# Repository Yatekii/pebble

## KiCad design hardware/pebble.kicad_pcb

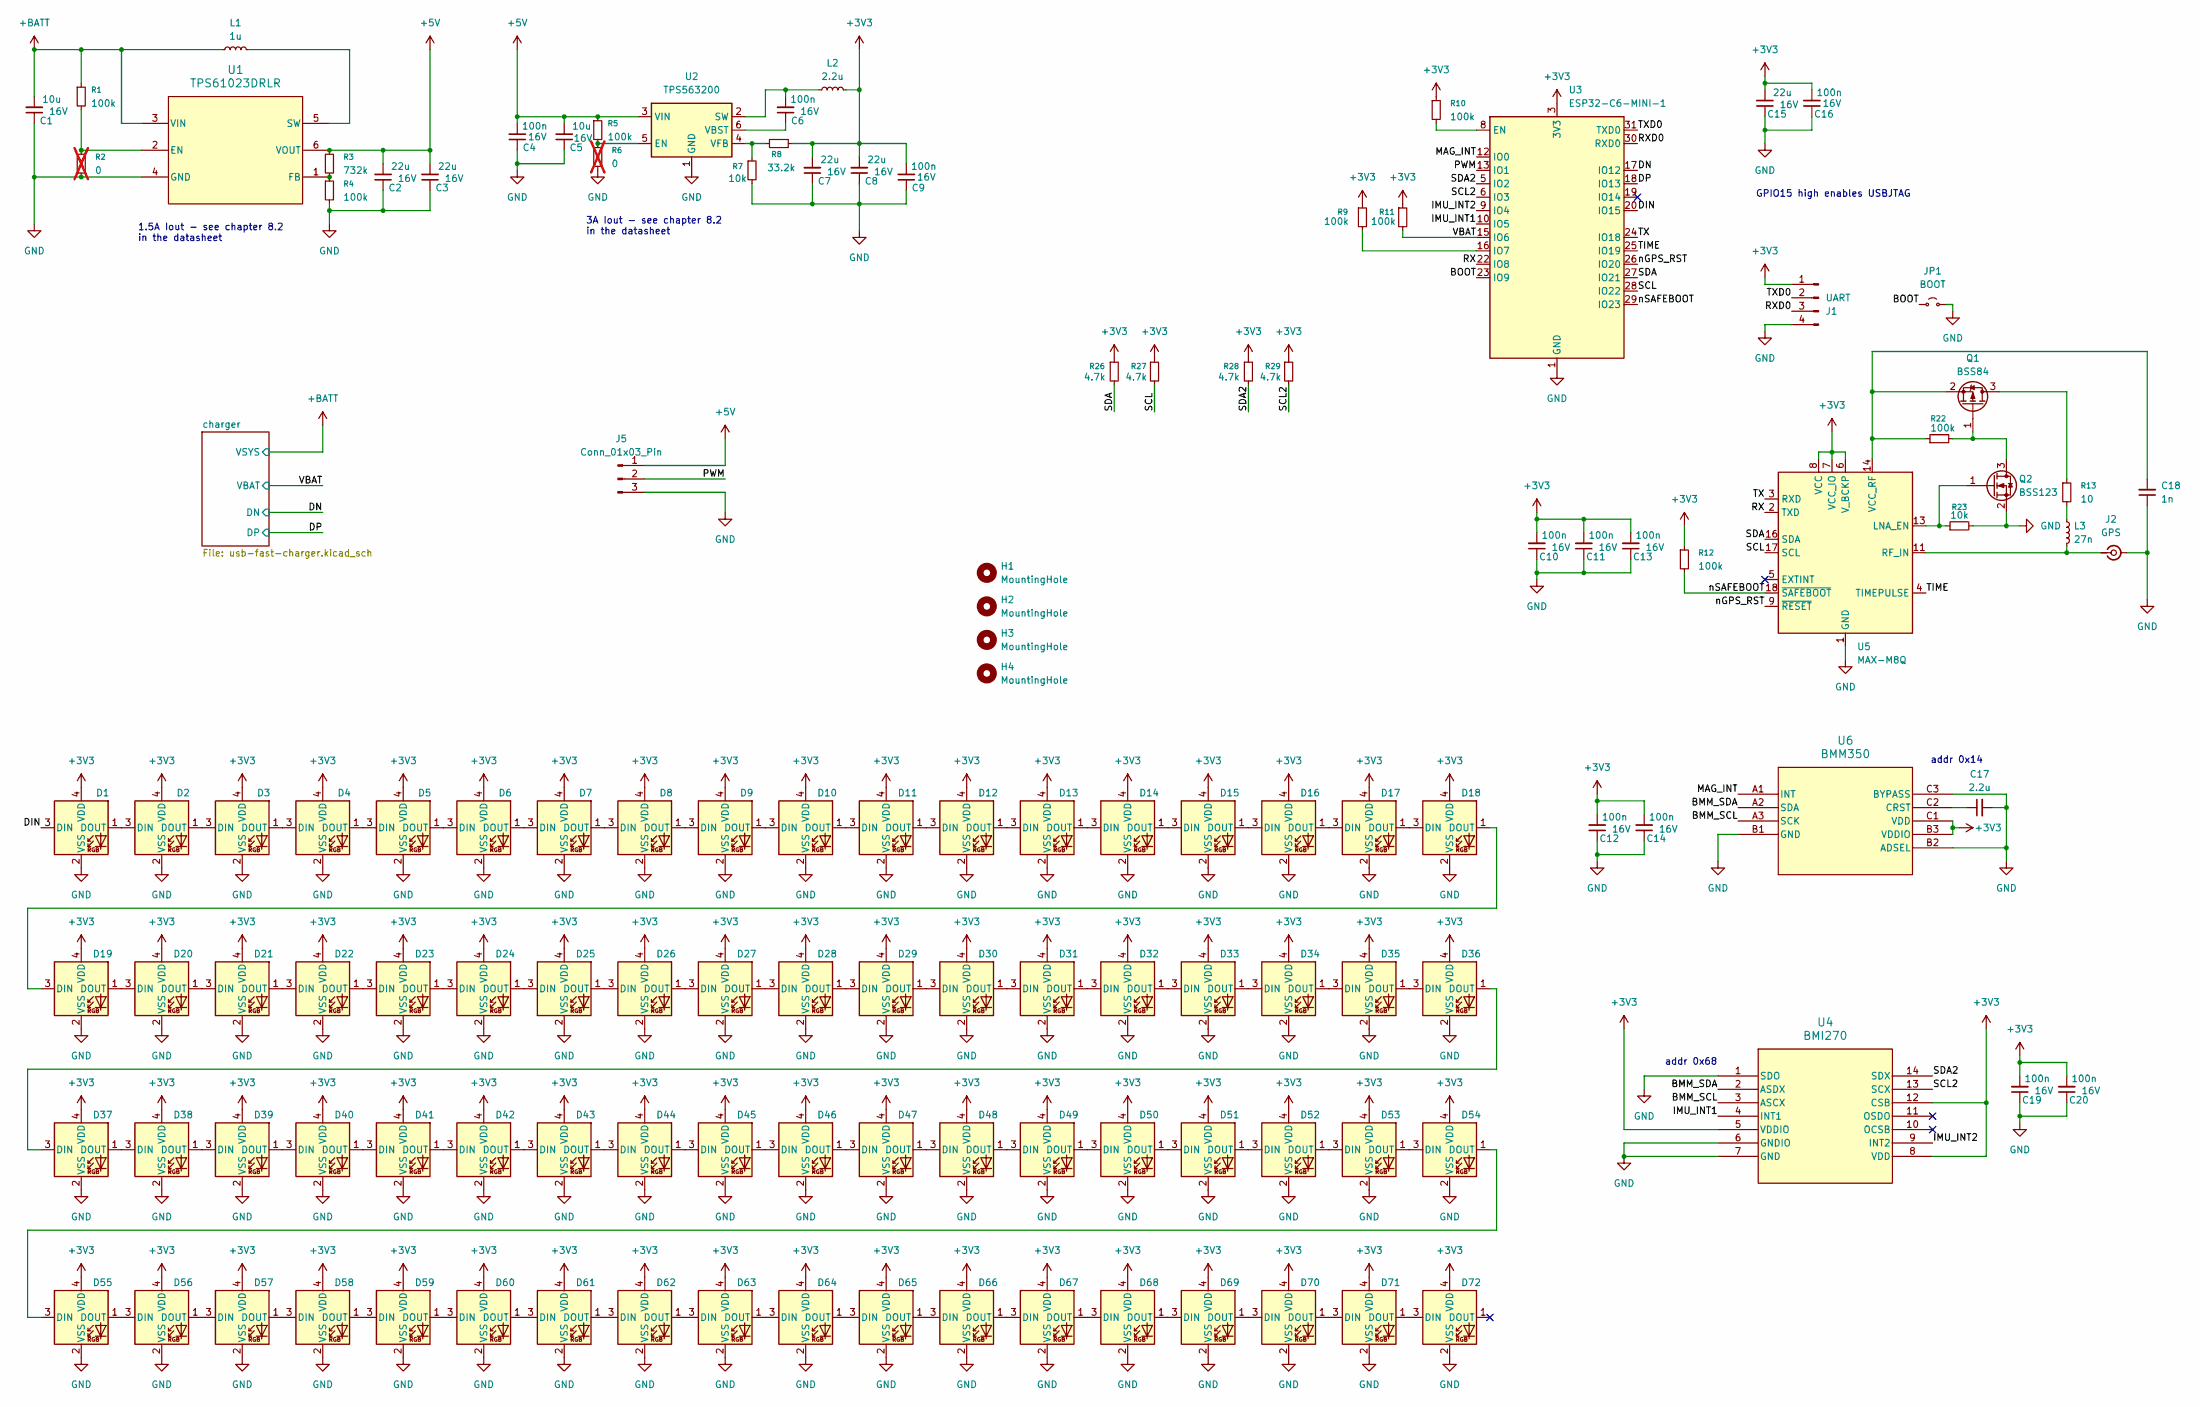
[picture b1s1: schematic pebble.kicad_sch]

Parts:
C1, C5: 10u; C_0603_1608Metric; Rating 16V
C2, C3, C7, C8, C15: 22u; C_0603_1608Metric; Rating 16V
C4, C6, C9, C10, C11, C12, C13, C14, C16, C19, C20: 100n; C_0402_1005Metric; Rating 16V
C17: 2.2u; C_0402_1005Metric
C18: 1n; C_0402_1005Metric
D1: WS2812B-2020; LED_WS2812B-2020_PLCC4_2.0x2.0mm; LCSC Part # C965555
D2, D3, D4, D5, D6, D7, D8, D9, D10, D11, D12, D13, D14, D15, D16, D17, D18, D19, D20, D21, D22, D23, D24, D25, D26, D27, D28, D29, D30, D31, D32, D33, D34, D35, D36, D37, D38, D39, D40, D41, D42, D43, D44, D45, D46, D47, D48, D49, D50, D51, D52, D53, D54, D55, D56, D57, D58, D59, D60, D61, D62, D63, D64, D65, D66, D67, D68, D69, D70, D71, D72: WS2812B-2020; LED_WS2812B-2020_PLCC4_2.0x2.0mm
H1, H2, H3, H4: MountingHole; MountingHole_3.2mm_M3
J1: UART; PinHeader_1x04_P1.27mm_Vertical
J2: GPS; U.FL_Molex_MCRF_73412-0110_Vertical; LCSC Part # C22418213
J5: Conn_01x03_Pin; PinHeader_1x03_P1.27mm_Horizontal
JP1: BOOT; TestPoint_2Pads_Pitch2.54mm_Drill0.8mm
L1: 1u; L_Coilcraft_XxL4040; Part XEL4030-102MEC
L2: 2.2u; IND_SPM6530_TDK
L3: 27n; L_0402_1005Metric_Pad0.77x0.64mm_HandSolder; Part LQG15HS27NJ02
Q1: BSS84; SOT-23; LCSC Part # Part # C7420340
Q2: BSS123; SOT-23; LCSC Part # C7420338
R1, R4, R5, R9, R10, R11, R12, R22: 100k; R_0402_1005Metric
R2, R6: 0; R_0402_1005Metric; not fitted
R3: 732k; R_0402_1005Metric
R7, R23: 10k; R_0402_1005Metric
R8: 33.2k; R_0402_1005Metric
R13: 10; R_0402_1005Metric
R26, R27, R28, R29: 4.7k; R_0402_1005Metric
U1: TPS61023DRLR; SOT-563; LCSC Part # C919459
U2: TPS563200; SOT-23-6; Part SPM6530T-2R2M; LCSC Part # C97253
U3: ESP32-C6-MINI-1; LCSC Part # C5736265
U4: BMI270; BMI270_BOS; LCSC Part # C2836813
U5: MAX-M8Q; ublox_MAX; LCSC Part # C6898733
U6: BMM350; BGA9_BMM350_BOS; LCSC Part # C17225907

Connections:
+3V3: C7.2, C8.2, C9.2, C10.2, C11.2, C12.2, C13.2, C14.2, C15.2, C16.2, C19.2, C20.2, D1.4 (VDD), D2.4 (VDD), D3.4 (VDD), D4.4 (VDD), D5.4 (VDD), D6.4 (VDD), D7.4 (VDD), D8.4 (VDD), D9.4 (VDD), D10.4 (VDD), D11.4 (VDD), D12.4 (VDD), D13.4 (VDD), D14.4 (VDD), D15.4 (VDD), D16.4 (VDD), D17.4 (VDD), D18.4 (VDD), D19.4 (VDD), D20.4 (VDD), D21.4 (VDD), D22.4 (VDD), D23.4 (VDD), D24.4 (VDD), D25.4 (VDD), D26.4 (VDD), D27.4 (VDD), D28.4 (VDD), D29.4 (VDD), D30.4 (VDD), D31.4 (VDD), D32.4 (VDD), D33.4 (VDD), D34.4 (VDD), D35.4 (VDD), D36.4 (VDD), D37.4 (VDD), D38.4 (VDD), D39.4 (VDD), D40.4 (VDD), D41.4 (VDD), D42.4 (VDD), D43.4 (VDD), D44.4 (VDD), D45.4 (VDD), D46.4 (VDD), D47.4 (VDD), D48.4 (VDD), D49.4 (VDD), D50.4 (VDD), D51.4 (VDD), D52.4 (VDD), D53.4 (VDD), D54.4 (VDD), D55.4 (VDD), D56.4 (VDD), D57.4 (VDD), D58.4 (VDD), D59.4 (VDD), D60.4 (VDD), D61.4 (VDD), D62.4 (VDD), D63.4 (VDD), D64.4 (VDD), D65.4 (VDD), D66.4 (VDD), D67.4 (VDD), D68.4 (VDD), D69.4 (VDD), D70.4 (VDD), D71.4 (VDD), D72.4 (VDD), J1.1, L2.2, R8.1, R9.1, R10.1, R11.1, R12.1, R26.1, R27.1, R28.1, R29.1, U3.3 (3V3), U4.5 (VDDIO), U4.8 (VDD), U4.12 (CSB), U5.6 (V_BCKP), U5.7 (VCC_IO), U5.8 (VCC), U6.B3 (VDDIO), U6.C1 (VDD); also elsewhere on the board
+5V: C2.2, C3.2, C4.2, C5.2, J5.1, R3.1, R5.1, U1.6 (VOUT), U2.3 (VIN)
+BATT: C1.2, L1.1, R1.1, U1.3 (VIN); also elsewhere on the board
/BMM_SCL: U4.3 (ASCX), U6.A3 (SCK)
/BMM_SDA: U4.2 (ASDX), U6.A2 (SDA)
/BOOT: JP1.1 (A), U3.23 (IO9)
/DIN: D1.3 (DIN), U3.20 (IO15)
/DN: U3.17 (IO12); also elsewhere on the board
/DP: U3.18 (IO13); also elsewhere on the board
/IMU_INT1: U3.10 (IO5), U4.4 (INT1)
/IMU_INT2: U3.9 (IO4), U4.9 (INT2)
/MAG_INT: U3.12 (IO0), U6.A1 (INT)
/PWM: J5.2, U3.13 (IO1)
/RX: U3.22 (IO8), U5.2 (TXD)
/RXD0: J1.3, U3.30 (RXD0)
/SCL: R27.2, U3.28 (IO22), U5.17 (SCL)
/SCL2: R29.2, U3.6 (IO3), U4.13 (SCX)
/SDA: R26.2, U3.27 (IO21), U5.16 (SDA)
/SDA2: R28.2, U3.5 (IO2), U4.14 (SDX)
/TIME: U3.25 (IO19), U5.4 (TIMEPULSE)
/TX: U3.24 (IO18), U5.3 (RXD)
/TXD0: J1.2, U3.31 (TXD0)
/VBAT: R11.2, U3.15 (IO6); also elsewhere on the board
/nGPS_RST: U3.26 (IO20), U5.9 (~RESET)
/nSAFEBOOT: R12.2, U3.29 (IO23), U5.18 (~SAFEBOOT)
GND: C1.1, C2.1, C3.1, C4.1, C5.1, C7.1, C8.1, C9.1, C10.1, C11.1, C12.1, C13.1, C14.1, C15.1, C16.1, C17.2, C18.1, C19.1, C20.1, D1.2 (VSS), D2.2 (VSS), D3.2 (VSS), D4.2 (VSS), D5.2 (VSS), D6.2 (VSS), D7.2 (VSS), D8.2 (VSS), D9.2 (VSS), D10.2 (VSS), D11.2 (VSS), D12.2 (VSS), D13.2 (VSS), D14.2 (VSS), D15.2 (VSS), D16.2 (VSS), D17.2 (VSS), D18.2 (VSS), D19.2 (VSS), D20.2 (VSS), D21.2 (VSS), D22.2 (VSS), D23.2 (VSS), D24.2 (VSS), D25.2 (VSS), D26.2 (VSS), D27.2 (VSS), D28.2 (VSS), D29.2 (VSS), D30.2 (VSS), D31.2 (VSS), D32.2 (VSS), D33.2 (VSS), D34.2 (VSS), D35.2 (VSS), D36.2 (VSS), D37.2 (VSS), D38.2 (VSS), D39.2 (VSS), D40.2 (VSS), D41.2 (VSS), D42.2 (VSS), D43.2 (VSS), D44.2 (VSS), D45.2 (VSS), D46.2 (VSS), D47.2 (VSS), D48.2 (VSS), D49.2 (VSS), D50.2 (VSS), D51.2 (VSS), D52.2 (VSS), D53.2 (VSS), D54.2 (VSS), D55.2 (VSS), D56.2 (VSS), D57.2 (VSS), D58.2 (VSS), D59.2 (VSS), D60.2 (VSS), D61.2 (VSS), D62.2 (VSS), D63.2 (VSS), D64.2 (VSS), D65.2 (VSS), D66.2 (VSS), D67.2 (VSS), D68.2 (VSS), D69.2 (VSS), D70.2 (VSS), D71.2 (VSS), D72.2 (VSS), J1.4, J2.2 (Ext), J5.3, JP1.2 (B), Q2.2 (S), R2.2, R4.2, R6.2, R7.2, R23.2, U1.4 (GND), U2.1 (GND), U3.1 (GND), U3.2 (GND), U3.11 (GND), U3.14 (GND), U3.36 (GND), U3.37 (GND), U3.38 (GND), U3.39 (GND), U3.40 (GND), U3.41 (GND), U3.42 (GND), U3.43 (GND), U3.44 (GND), U3.45 (GND), U3.46 (GND), U3.47 (GND), U3.48 (GND), U3.49 (GND), U3.50 (GND), U3.51 (GND), U3.52 (GND), U3.53 (GND), U4.1 (SDO), U4.6 (GNDIO), U4.7 (GND), U5.1 (GND), U5.10 (GND), U5.12 (GND), U6.B1 (GND), U6.B2 (ADSEL), U6.C3 (BYPASS); also elsewhere on the board
unnamed: D1.1 (DOUT), D2.3 (DIN)
unnamed: D2.1 (DOUT), D3.3 (DIN)
unnamed: D3.1 (DOUT), D4.3 (DIN)
unnamed: D4.1 (DOUT), D5.3 (DIN)
unnamed: D5.1 (DOUT), D6.3 (DIN)
unnamed: D6.1 (DOUT), D7.3 (DIN)
unnamed: D7.1 (DOUT), D8.3 (DIN)
unnamed: D8.1 (DOUT), D9.3 (DIN)
unnamed: D9.1 (DOUT), D10.3 (DIN)
unnamed: D10.1 (DOUT), D11.3 (DIN)
unnamed: D11.1 (DOUT), D12.3 (DIN)
unnamed: D12.1 (DOUT), D13.3 (DIN)
unnamed: D13.1 (DOUT), D14.3 (DIN)
unnamed: D14.1 (DOUT), D15.3 (DIN)
unnamed: D15.1 (DOUT), D16.3 (DIN)
unnamed: D16.1 (DOUT), D17.3 (DIN)
unnamed: D17.1 (DOUT), D18.3 (DIN)
unnamed: D18.1 (DOUT), D19.3 (DIN)
unnamed: D19.1 (DOUT), D20.3 (DIN)
unnamed: D20.1 (DOUT), D21.3 (DIN)
unnamed: D21.1 (DOUT), D22.3 (DIN)
unnamed: D22.1 (DOUT), D23.3 (DIN)
unnamed: D23.1 (DOUT), D24.3 (DIN)
unnamed: D24.1 (DOUT), D25.3 (DIN)
unnamed: D25.1 (DOUT), D26.3 (DIN)
unnamed: D26.1 (DOUT), D27.3 (DIN)
unnamed: D27.1 (DOUT), D28.3 (DIN)
unnamed: D28.1 (DOUT), D29.3 (DIN)
unnamed: D29.1 (DOUT), D30.3 (DIN)
unnamed: D30.1 (DOUT), D31.3 (DIN)
unnamed: D31.1 (DOUT), D32.3 (DIN)
unnamed: D32.1 (DOUT), D33.3 (DIN)
unnamed: D33.1 (DOUT), D34.3 (DIN)
unnamed: D34.1 (DOUT), D35.3 (DIN)
unnamed: D35.1 (DOUT), D36.3 (DIN)
unnamed: D36.1 (DOUT), D37.3 (DIN)
unnamed: D37.1 (DOUT), D38.3 (DIN)
unnamed: D38.1 (DOUT), D39.3 (DIN)
unnamed: D39.1 (DOUT), D40.3 (DIN)
unnamed: D40.1 (DOUT), D41.3 (DIN)
unnamed: D41.1 (DOUT), D42.3 (DIN)
unnamed: D42.1 (DOUT), D43.3 (DIN)
unnamed: D43.1 (DOUT), D44.3 (DIN)
unnamed: D44.1 (DOUT), D45.3 (DIN)
unnamed: D45.1 (DOUT), D46.3 (DIN)
unnamed: D46.1 (DOUT), D47.3 (DIN)
unnamed: D47.1 (DOUT), D48.3 (DIN)
unnamed: D48.1 (DOUT), D49.3 (DIN)
unnamed: D49.1 (DOUT), D50.3 (DIN)
unnamed: D50.1 (DOUT), D51.3 (DIN)
unnamed: D51.1 (DOUT), D52.3 (DIN)
unnamed: D52.1 (DOUT), D53.3 (DIN)
unnamed: D53.1 (DOUT), D54.3 (DIN)
unnamed: D54.1 (DOUT), D55.3 (DIN)
unnamed: D55.1 (DOUT), D56.3 (DIN)
unnamed: D56.1 (DOUT), D57.3 (DIN)
unnamed: D57.1 (DOUT), D58.3 (DIN)
unnamed: D58.1 (DOUT), D59.3 (DIN)
unnamed: D59.1 (DOUT), D60.3 (DIN)
unnamed: D60.1 (DOUT), D61.3 (DIN)
unnamed: D61.1 (DOUT), D62.3 (DIN)
unnamed: D62.1 (DOUT), D63.3 (DIN)
unnamed: D63.1 (DOUT), D64.3 (DIN)
unnamed: D64.1 (DOUT), D65.3 (DIN)
unnamed: D65.1 (DOUT), D66.3 (DIN)
unnamed: D66.1 (DOUT), D67.3 (DIN)
unnamed: D67.1 (DOUT), D68.3 (DIN)
unnamed: D68.1 (DOUT), D69.3 (DIN)
unnamed: D69.1 (DOUT), D70.3 (DIN)
unnamed: D70.1 (DOUT), D71.3 (DIN)
unnamed: D71.1 (DOUT), D72.3 (DIN)
unnamed: J2.1 (In), L3.2, U5.11 (RF_IN)
unnamed: L3.1, R13.2
unnamed: Q1.3 (D), R13.1
unnamed: Q1.1 (G), Q2.3 (D), R22.2
unnamed: C18.2, Q1.2 (S), R22.1, U5.14 (VCC_RF)
unnamed: Q2.1 (G), R23.1, U5.13 (LNA_EN)
unnamed: R1.2, R2.1, U1.2 (EN)
unnamed: R3.2, R4.1, U1.1 (FB)
unnamed: L1.2, U1.5 (SW)
unnamed: R5.2, R6.1, U2.5 (EN)
unnamed: C6.2, L2.1, U2.2 (SW)
unnamed: C6.1, U2.6 (VBST)
unnamed: R7.1, R8.2, U2.4 (VFB)
unnamed: R10.2, U3.8 (EN)
unnamed: R9.2, U3.16 (IO7)
unnamed: C17.1, U6.C2 (CRST)

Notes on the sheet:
addr 0x14
GPIO15 high enables USBJTAG
3A Iout - see chapter 8.2 in the datasheet
1.5A Iout - see chapter 8.2 in the datasheet
addr 0x68

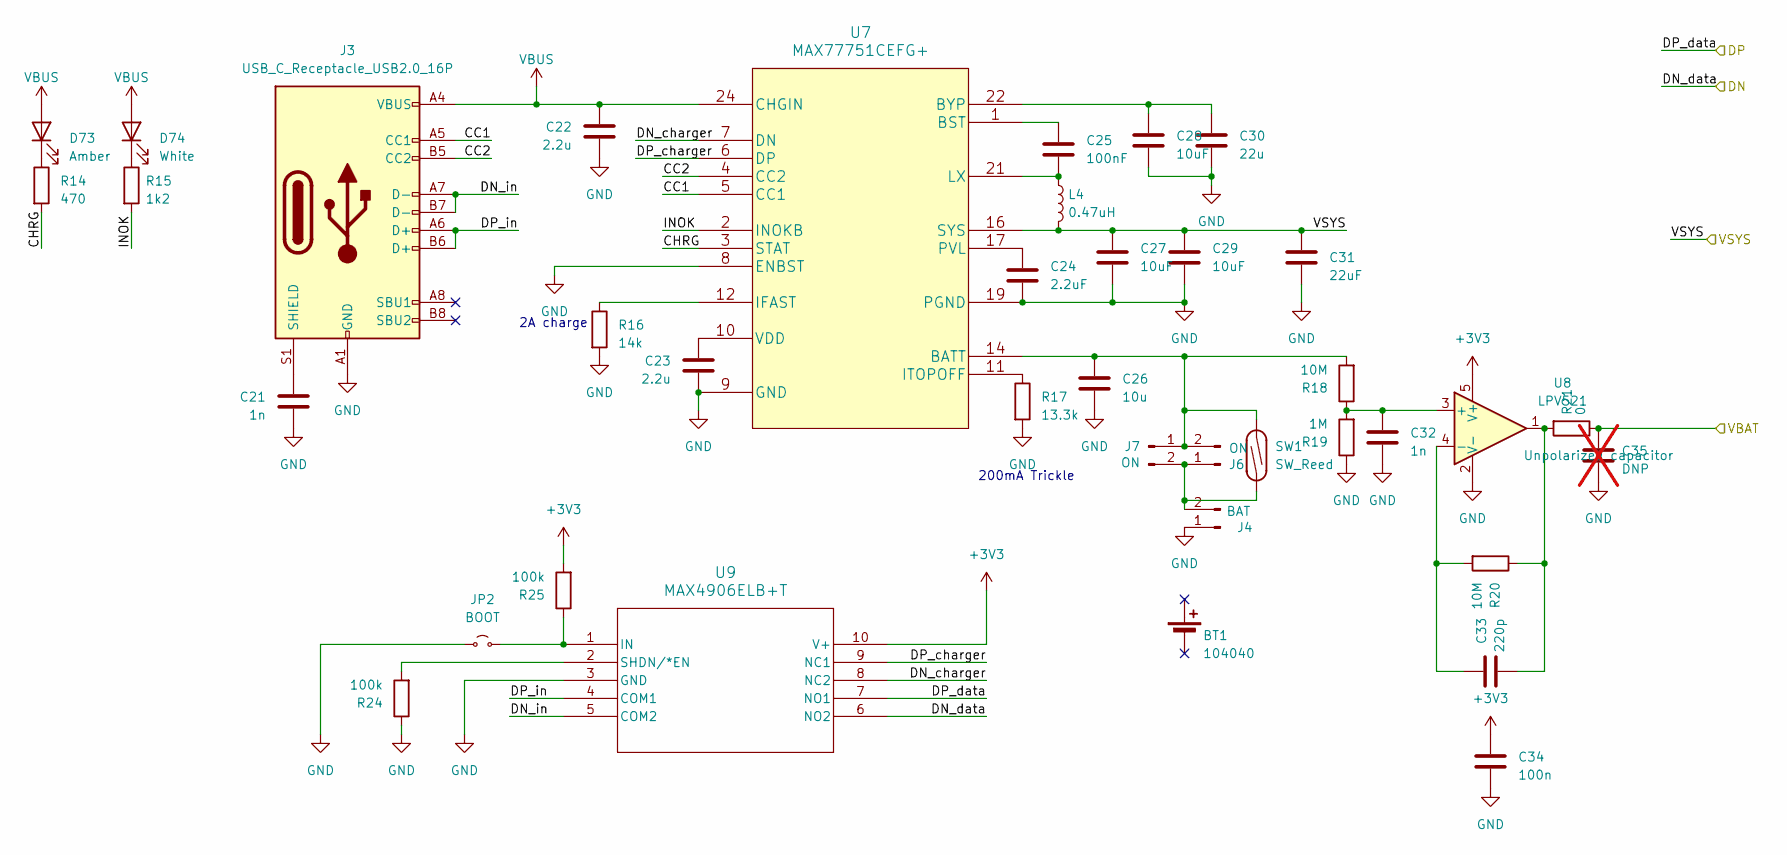
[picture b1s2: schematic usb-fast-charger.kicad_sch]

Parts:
BT1: 104040; JST_PH_S2B-PH-SM4-TB_1x02-1MP_P2.00mm_Horizontal
C21: 1n; C_1206_3216Metric; Voltage 2000; Mouser 80-C1206C102KGR
C22, C23: 2.2u; C_0402_1005Metric; Voltage 16; Mouser 346-CM05X5R225M16AH
C24: 2.2uF; C_0402_1005Metric; Voltage 16; Mouser 346-CM05X5R225M16AH
C25: 100nF; C_0402_1005Metric; Voltage 25V
C26: 10u; C_0805_2012Metric; Voltage 16; Mouser 187-CL21A106KOQNNNE
C27, C28, C29: 10uF; C_0805_2012Metric; Voltage 16; Mouser 187-CL21A106KOQNNNE
C30: 22u; C_0805_2012Metric; Voltage 16; Mouser 187-CL21A226MOQNNNE
C31: 22uF; C_0805_2012Metric; Voltage 16; Mouser 187-CL21A226MOQNNNE
C32: 1n; C_0402_1005Metric; Voltage 25V
C33: 220p; C_0402_1005Metric; Voltage 25V
C34: 100n; C_0402_1005Metric; Voltage 25V
C35: DNP; C_0402_1005Metric; Voltage 25V; not fitted
D73: Amber; LED_0603_1608Metric; Mouser 710-150060AS75000
D74: White; LED_0603_1608Metric; Mouser 78-VLMW1300-GS08
J3: USB_C_Receptacle_USB2.0_16P; USB_C_Receptacle_G-Switch_GT-USB-7051x; LCSC Part # C2843970
J4: BAT; PinHeader_1x02_P1.27mm_Vertical
J6, J7: ON; PinHeader_1x02_P1.27mm_Vertical
JP2: BOOT; TestPoint_2Pads_Pitch2.54mm_Drill0.8mm
L4: 0.47uH; IND_SRP2512TMA_BRN; Mouser 652-SRP2512TMA-R47M
R14: 470; R_0402_1005Metric
R15: 1k2; R_0402_1005Metric
R16: 14k; R_0402_1005Metric; Mouser 603-AC0402FR-0714KL
R17: 13.3k; R_0402_1005Metric; Mouser 603-RC0402FR-0713K3L
R18, R20: 10M; R_0402_1005Metric; Mouser 603-AC0402FR-0710ML
R19: 1M; R_0402_1005Metric; Mouser 603-AC0402FR-071ML
R21: 0; R_0402_1005Metric
R24, R25: 100k; R_0402_1005Metric; Mouser 603-AC0402FR-071ML
SW1: SW_Reed; 59170-1-S-00-D; LCSC Part # C315909
U7: MAX77751CEFG+; LCSC Part # C2908590
U8: LPV521; SOT-23-5; LCSC Part # C779403
U9: MAX4906ELB+T; 21-0164_L1022&plus_1_MXM; LCSC Part # C2150885

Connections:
+3V3: C34.1, R25.2, U8.5 (V+), U9.10 (V+); also elsewhere on the board
+BATT: C27.1, C29.1, C31.1, L4.2, U7.15 (SYS), U7.16 (SYS); also elsewhere on the board
/DN: U9.6 (NO2); also elsewhere on the board
/DP: U9.7 (NO1); also elsewhere on the board
/VBAT: C35.1, R21.1; also elsewhere on the board
/charger/CC1: J3.A5 (CC1), U7.5 (CC1)
/charger/CC2: J3.B5 (CC2), U7.4 (CC2)
/charger/CHRG: R14.2, U7.3 (STAT)
/charger/DN_charger: U7.7 (DN), U9.8 (NC2)
/charger/DN_in: J3.A7 (D-), J3.B7 (D-), U9.5 (COM2)
/charger/DP_charger: U7.6 (DP), U9.9 (NC1)
/charger/DP_in: J3.A6 (D+), J3.B6 (D+), U9.4 (COM1)
/charger/INOK: R15.2, U7.2 (INOKB)
GND: C21.2, C22.2, C23.2, C24.2, C26.2, C27.2, C28.2, C29.2, C30.2, C31.2, C32.2, C34.2, C35.2, J3.A1 (GND), J3.A12 (GND), J3.B1 (GND), J3.B12 (GND), J4.1, JP2.1 (A), R16.2, R17.2, R19.1, R24.1, U7.8 (ENBST), U7.9 (GND), U7.18 (PGND), U7.19 (PGND), U8.2 (V-), U9.3 (GND); also elsewhere on the board
unnamed: C25.2, L4.1, U7.20 (LX), U7.21 (LX)
unnamed: C33.1, R20.1, R21.2, U8.1
unnamed: D73.1 (K), R14.1
unnamed: D74.1 (K), R15.1
unnamed: C21.1, J3.S1 (SHIELD)
unnamed: J4.2, J6.1, J7.2, SW1.2
unnamed: C26.1, J6.2, J7.1, R18.2, SW1.1, U7.13 (BATT), U7.14 (BATT)
unnamed: JP2.2 (B), R25.1, U9.1 (IN)
unnamed: C25.1, U7.1 (BST)
unnamed: C28.1, C30.1, U7.22 (BYP)
unnamed: R16.1, U7.12 (IFAST)
unnamed: R17.1, U7.11 (ITOPOFF)
unnamed: C24.1, U7.17 (PVL)
unnamed: C23.1, U7.10 (VDD)
unnamed: C32.1, R18.1, R19.2, U8.3 (+)
unnamed: C33.2, R20.2, U8.4 (-)
unnamed: R24.2, U9.2 (SHDN/*EN)
VBUS: C22.1, D73.2 (A), D74.2 (A), J3.A4 (VBUS), J3.A9 (VBUS), J3.B4 (VBUS), J3.B9 (VBUS), U7.23 (CHGIN), U7.24 (CHGIN)

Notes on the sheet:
200mA Trickle
2A charge

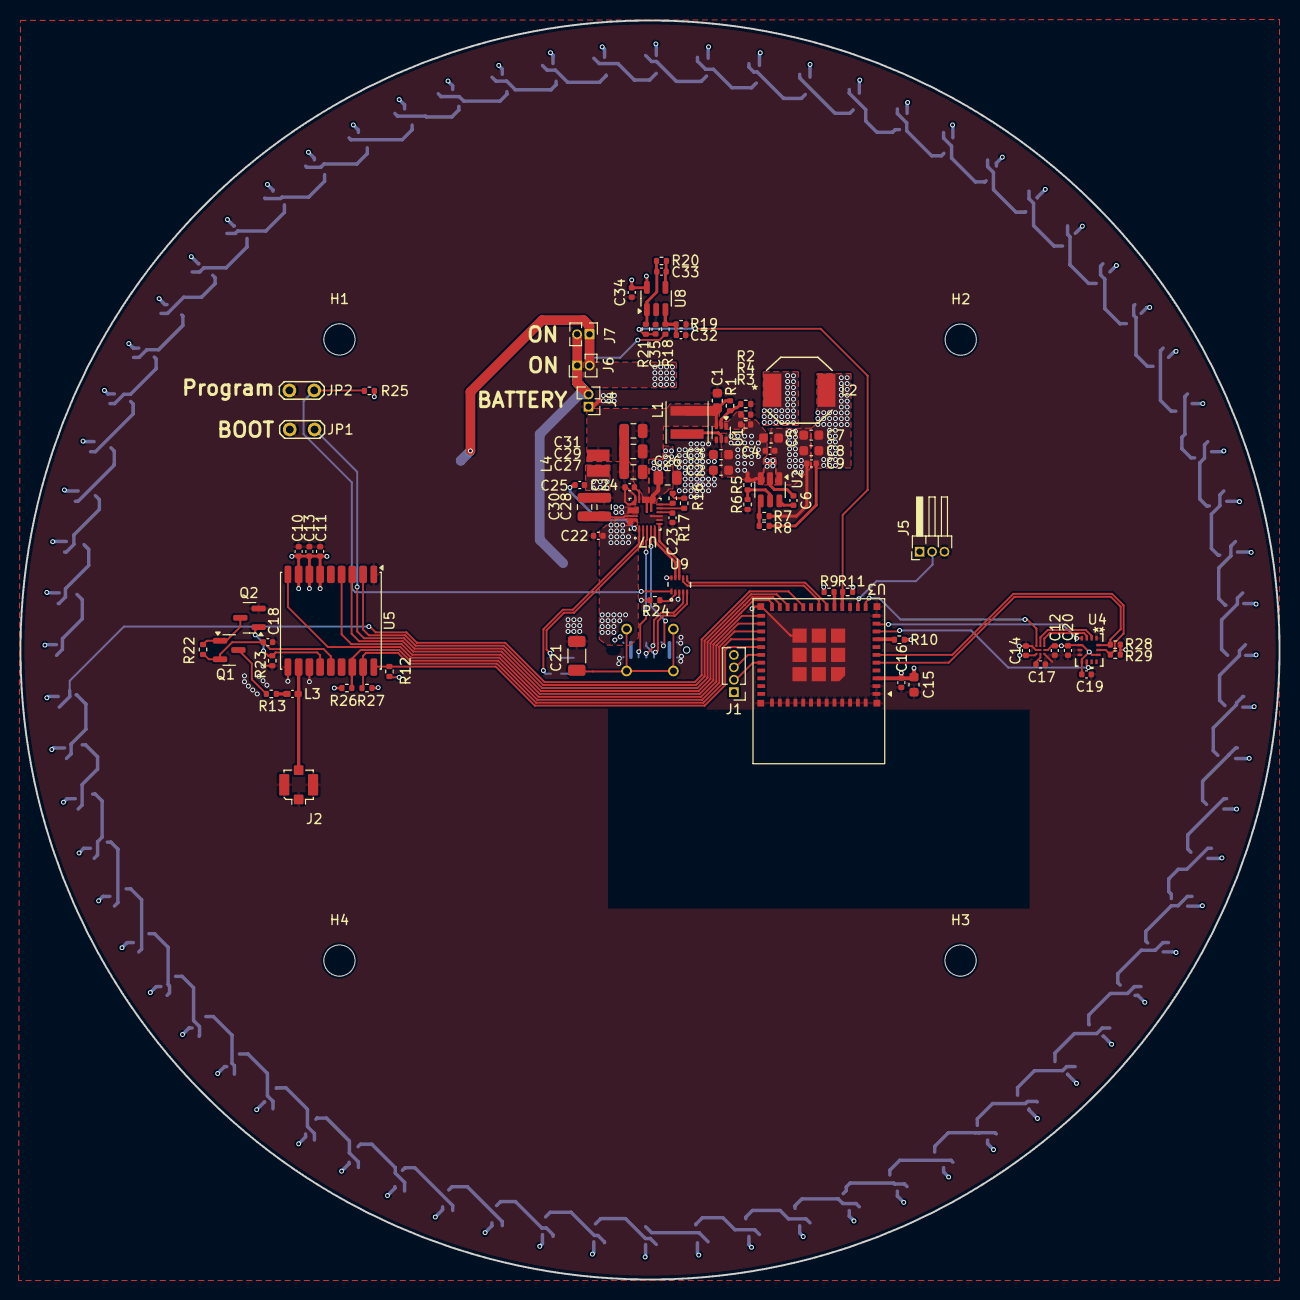
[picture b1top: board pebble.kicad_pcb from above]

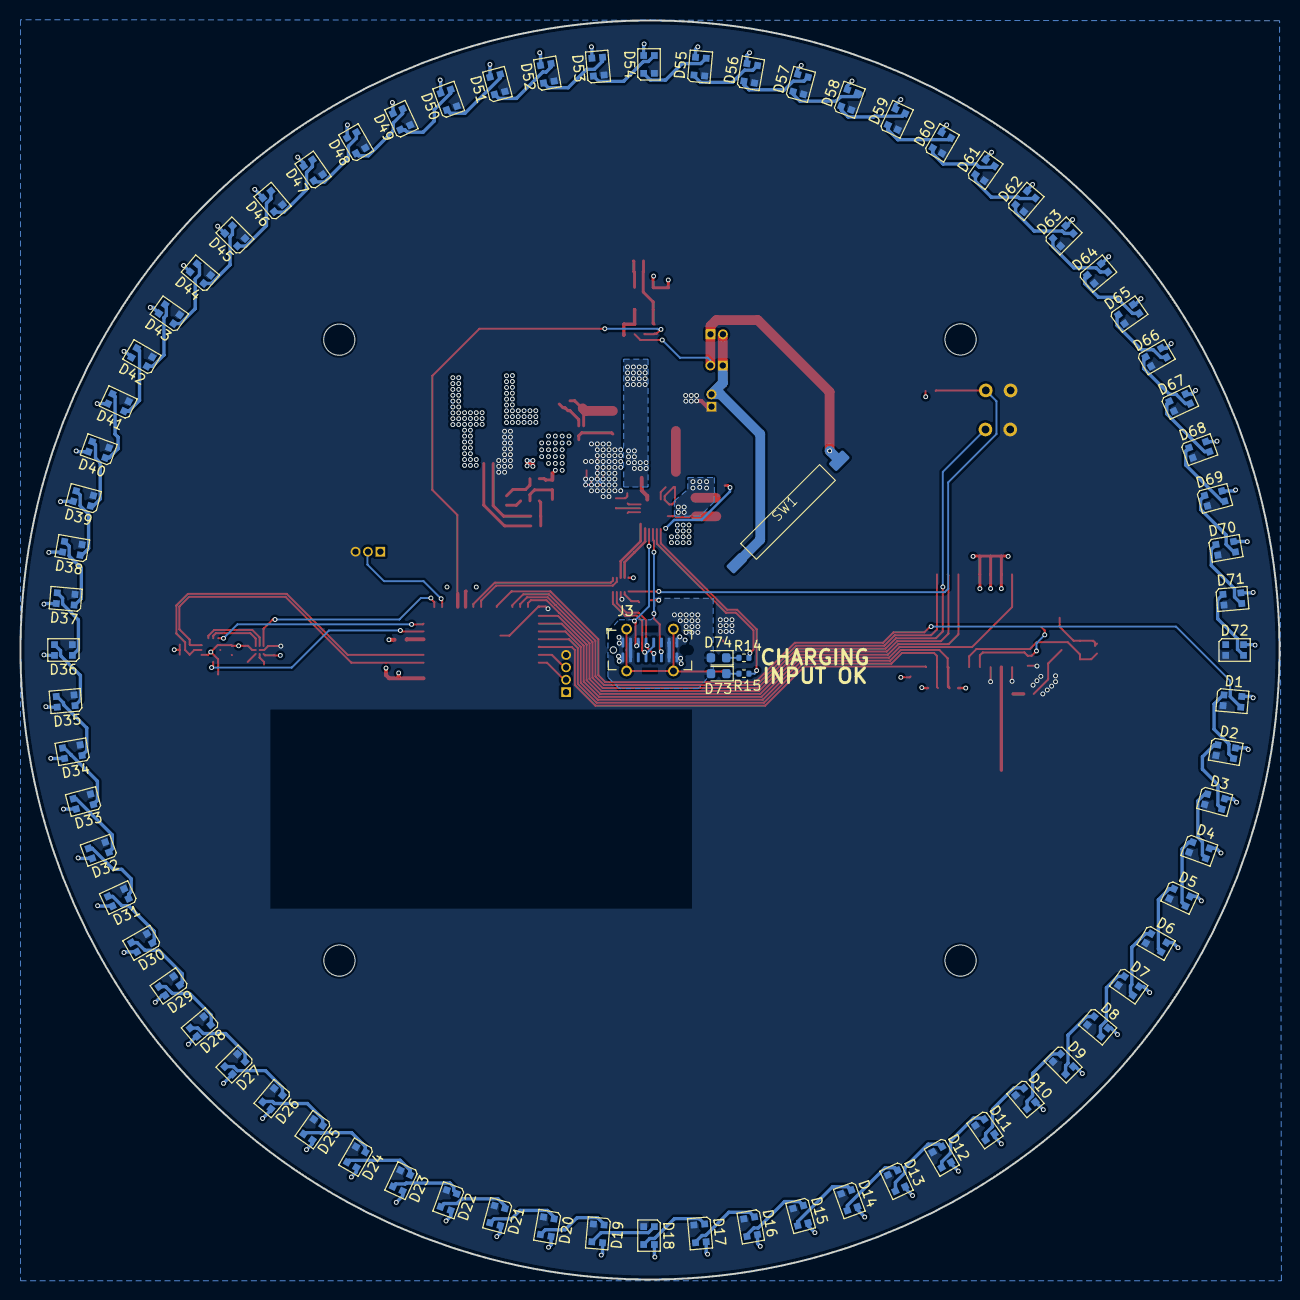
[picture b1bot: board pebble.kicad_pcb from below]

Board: 4 copper layers, 129.0 x 129.0 mm, 167 parts (78 on the bottom side), 139 nets.

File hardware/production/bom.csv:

Designator,Footprint,Quantity,Value,LCSC Part #
"C1, C5",0603,2,10u,
"C10, C11, C12, C13, C14, C16, C19, C20, C34, C4, C6, C9",0402,12,100n,
"C15, C2, C3, C7, C8",0603,5,22u,
"C17, C22, C23",0402,3,2.2u,
"C18, C32",0402,2,1n,
C21,1206,1,1n,
C24,0402,1,2.2uF,
C25,0402,1,100nF,
C26,0805,1,10u,
"C27, C28, C29",0805,3,10uF,
C30,0805,1,22u,
C31,0805,1,22uF,
C33,0402,1,220p,
D1,LED_WS2812B-2020_PLCC4_2.0x2.0mm,1,WS2812B-2020,C965555
"D10, D11, D12, D13, D14, D15, D16, D17, D18, D19, D2, D20, D21, D22, D23, D24, D25, D26, D27, D28, D29, D3, D30, D31, D32, D33, D34, D35, D36, D37, D38, D39, D4, D40, D41, D42, D43, D44, D45, D46, D47, D48, D49, D5, D50, D51, D52, D53, D54, D55, D56, D57, D58, D59, D6, D60, D61, D62, D63, D64, D65, D66, D67, D68, D69, D7, D70, D71, D72, D8, D9",LED_WS2812B-2020_PLCC4_2.0x2.0mm,71,WS2812B-2020,
D73,0603,1,Amber,
D74,0603,1,White,
J1,PinHeader_1x04_P1.27mm_Vertical,1,UART,
J2,U.FL_Molex_MCRF_73412-0110_Vertical,1,GPS,C22418213
J3,USB_C_Receptacle_G-Switch_GT-USB-7051x,1,USB_C_Receptacle_USB2.0_16P,C2843970
J4,PinHeader_1x02_P1.27mm_Vertical,1,BAT,
J5,PinHeader_1x03_P1.27mm_Horizontal,1,Conn_01x03_Pin,
"J6, J7",PinHeader_1x02_P1.27mm_Vertical,2,ON,
"JP1, JP2",TestPoint_2Pads_Pitch2.54mm_Drill0.8mm,2,BOOT,
L1,L_Coilcraft_XxL4040,1,1u,
L2,IND_SPM6530_TDK,1,2.2u,
L3,0402,1,27n,
L4,IND_SRP2512TMA_BRN,1,0.47uH,
Q1,SOT-23,1,BSS84,
Q2,SOT-23,1,BSS123,C7420338
"R1, R10, R11, R12, R22, R24, R25, R4, R5, R9",0402,10,100k,
R13,0402,1,10,
R14,0402,1,470,
R15,0402,1,1k2,
R16,0402,1,14k,
R17,0402,1,13.3k,
"R18, R20",0402,2,10M,
R19,0402,1,1M,
R21,0402,1,0,
"R23, R7",0402,2,10k,
"R26, R27, R28, R29",0402,4,4.7k,
R3,0402,1,732k,
R8,0402,1,33.2k,
SW1,59170-1-S-00-D,1,SW_Reed,C315909
U1,SOT-563,1,TPS61023DRLR,C919459
U2,SOT-23-6,1,TPS563200,C97253
U3,ESP32-C6-MINI-1,1,ESP32-C6-MINI-1,C97253
U4,BMI270_BOS,1,BMI270,C2836813
U5,ublox_MAX,1,MAX-M8Q,C6898733
U6,BGA9_BMM350_BOS,1,BMM350,C17225907
U7,MAX77751CEFG+,1,MAX77751CEFG+,C2908590
U8,SOT-23-5,1,LPV521,C779403
U9,21-0164_L1022&plus_1_MXM,1,MAX4906ELB+T,C2150885

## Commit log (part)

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2025-11-22 initial design
2025-11-23 finalize rev0
2025-11-23 add gitignore
2025-11-23 remove clutter
2025-11-24 put charger leds on the back layer, position imu precisely, simplify schema, tapeout
2025-12-16 add nix flake and initial esp32-c6 project structure with probe-rs and defmt
2025-12-16 use esp-generate for fun and profit and we can run fw :)
2025-12-16 add claude instructions
2025-12-16 sending acc data via ble works
2025-12-16 add a small ui for data inspection
2025-12-16 fruitless tries to talk to the magnetometer
2025-12-16 make the loading/connecting screen nicer
2025-12-17 visualize the leds
2025-12-17 led colors broadcast over BLE properly
2025-12-17 LED goes in a circle now
2025-12-17 render the LEDs
2025-12-17 enable debug assertions
2025-12-17 rearrange layout to be more useful and beautiful
2025-12-17 beautify charts
2025-12-17 add ahrs filtering and broadcast it and gps via ble
2025-12-17 visualize gps and ahrs
2025-12-17 precisize for claude
2025-12-17 also visualize the satelites
2025-12-17 add a dummy UI for the puzzles
2025-12-18 compass works
2025-12-18 add the servo hal and compass functionality
2025-12-19 move shared i2c to a separate module
2025-12-19 move imu constants to a module
2025-12-19 add uom data and restructure modules a bit
2025-12-20 split up magnetometer code and imu code
2025-12-21 various cleanup
2025-12-21 document magic calibration numbers
2025-12-21 add storage hal bits to store puzzle state
2026-01-07 debug ahrs
2026-01-07 add claude info for imu rotations
2026-01-07 remove old firmware
2026-01-07 fix: gracefully handle LED initialization failure
    Instead of panicking when LED initialization fails, the firmware now
    continues without LED support. The LED task accepts Option<LedStrip>
    and simply does nothing if LEDs are unavailable.
    This allows the device to remain functional for core features even
    if there's a hardware issue with the LED strip.
2026-01-07 fix: handle NaN values in chart tick sorting
    partial_cmp returns None for NaN values, which would cause unwrap()
    to panic. Now uses unwrap_or(Equal) to treat NaN values as equal,
    preventing crashes when chart data contains invalid float values.
2026-01-07 fix: remove broken I2C bus scan function
    The scan_i2c_bus function was using self.i2c.write(&[]) which always
    wrote to the fixed BMI270 address instead of scanning different
    addresses. Since this debugging utility was unused and incorrect,
    it's removed to avoid confusion.
2026-01-07 firmware: replace unwrap/expect with proper error handling
    - GPS init now returns Result, task handles Option<Gps>
    - Servo timer init now returns Result
    - BLE init uses match instead of expect
    - I2C init uses match instead of expect
    - GATT server creation uses match instead of expect
    - Watch receiver() calls use let-else with error logging
2026-01-07 gui: replace unwrap/expect with proper error handling
    - HTTP client creation now returns Result, handled in run_app()
    - BLE tokio runtime creation now uses match with error reporting
2026-01-07 gui: fix O(n) performance bug in IMU data history
    Replace Vec with VecDeque for IMU history storage. This changes
    push operations from O(n) (due to Vec::remove(0) shifting all elements)
    to O(1) using VecDeque::pop_front() and push_back().
2026-01-07 firmware: add input validation for BLE LED commands
    - Validate LED index (0-71 for individual, or special values 0xFE/0xFF/0xF0-F2)
    - Log warnings for invalid/short commands instead of silently ignoring
    - Use named constants for special LED index values
    - Consistent early-return pattern for validation errors
2026-01-07 firmware: add device status reporting via BLE
    - Add DeviceStatus struct with PeripheralStatus enum for each peripheral
    - Add PeripheralError enum with error codes (InitFailed, I2cError, etc.)
    - Add device_status BLE characteristic (UUID ...defb, 16 bytes)
    - Track init status for LEDs, GPS, servo, IMU, magnetometer
    - Broadcast status after init and notify connected clients
    - Serialize as [status, error] byte pairs for each peripheral
2026-01-07 gui: add device status panel showing peripheral init status
    - Add DeviceStatusData and PeripheralStatusData structs to parse BLE data
    - Add DEVICE_STATUS_UUID and subscribe to notifications
    - Read device status on connect and display in new panel
    - Create DeviceStatusPanel component with status rows for each peripheral
    - Show OK/ERR status with error details when applicable
    - Integrate panel above puzzle list in right sidebar
2026-01-07 firmware: add filter layer and move AHRS from HAL
    Phase 1 of architecture restructure:
    - Create filter/ module for sensor fusion and state computation
    - Move ahrs.rs from hal/ to filter/ with enhanced documentation
    - Add filter/heading.rs with MagCalibration and compute_heading
    - Add filter/device_state.rs with DeviceState and GpsPosition structs
    - Update tasks/imu.rs to use filter module
2026-01-07 firmware: move state.rs content to filter/watches.rs
    Phase 2 of architecture restructure:
    - Create filter/watches.rs with organized watch channels
    - Group watches by category (sensor data, commands, status)
    - Add documentation for all types and channels
    - Add ServoCommand type for future use
    - Make state.rs a thin re-export layer for backwards compatibility
2026-01-07 firmware: add puzzle/control layer with state machine
    Phase 4 of architecture restructure:
    - Create puzzle/ module with state machine architecture
    - Add PuzzleStateMachine for tracking puzzle progression
    - Add PuzzleEvent and Action types for inter-layer communication
    - Add Puzzle trait for individual puzzle implementations
    - Implement CompassAlignPuzzle as first puzzle example
2026-01-07 firmware: refactor tasks to be command-driven
    Phase 5 of architecture restructure:
    - LED task now listens to LED_COMMAND watch for updates
    - Servo task now listens to SERVO_COMMAND watch
    - Keep run_compass as separate compass display task
    - Keep run_demo for servo testing
    - Add documentation for task categories
2026-01-07 firmware: add protocol-agnostic communications layer
    Phase 3 of architecture restructure:
    - Create comms/messages.rs with common message types
    - Add OutboundMessage and InboundMessage enums
    - Add PuzzleStateMessage for puzzle state reporting
    - Add PuzzleCommandMessage for external puzzle control
    - Document how to add new protocols (e.g., MQTT)
2026-01-07 firmware: add documentation to math module
    Phase 6 of architecture restructure:
    - Add module-level docs explaining coordinate systems
    - Document sensor orientations on PCB
    - Describe world frame conventions
2026-01-07 firmware: add tests for filter and puzzle modules
    Phase 7 of architecture restructure:
    - Add tests for heading computation (positive, negative, zero)
    - Add tests for magnetometer calibration (update, apply)
    - Add tests for PuzzleId (next, from_u8)
    - Add tests for SavedProgress serialization roundtrip
    - Add tests for PuzzleStateMachine (new, reset, from_saved)
2026-01-07 firmware: merge heading.rs into ahrs.rs
    The AHRS already computes tilt-compensated heading via yaw angle.
    - Add Orientation::heading() method for 0-360 normalization
    - Move MagCalibration to ahrs.rs (used before AHRS input)
    - Remove redundant filter/heading.rs module
    - Update IMU task to use orientation.heading()
2026-01-07 firmware: simplify MagCalibration::update with min/max
2026-01-08 firmware: fix GPS DisabledSentence error
    The nmea crate's Nmea::default() doesn't enable any sentence types.
    Use Nmea::create_for_navigation() to enable GGA, GSA, GSV, RMC, VTG, GLL.
    Also:
    - Add debug logging for raw NMEA sentences
    - Change parse error log from trace to warn
    - Use satellites in view count when no fix satellites available
2026-01-08 firmware: enable GPS + Galileo + GLONASS constellations for better satellite coverage
2026-01-08 firmware: fix AHRS magnetometer norm division by zero
    Wait for 50 samples of magnetometer calibration data before running
    AHRS filter. This prevents near-zero calibrated values during warmup
    from causing division by zero in the Madgwick filter normalization.
2026-01-08 firmware: revert multi-GNSS and add GPS factory reset
    The CFG-GNSS command was causing GPS malfunction. Revert to GPS-only
    and add a factory reset on init to clear any bad saved configuration.
2026-01-08 firmware: fix GPS NMEA parsing error for empty sentences
    - Reset buffer position and store '$' when starting a new sentence
    - Only buffer bytes after we've seen the '$' start marker
    - Check for minimum sentence length (>6 chars) before parsing
    - Add sentence content to parse error log for debugging
2026-01-08 docs: add nix develop instructions to CLAUDE.md
2026-01-08 firmware: silence GPS NMEA parse warnings for empty GSV sentences
    - Skip GSV sentences with 0 satellites (nmea crate can't parse them)
    - Downgrade parse errors to debug level (TXT and other unsupported
    sentences are expected to fail)
2026-01-08 firmware: properly handle GSV sentences with 0 satellites
    The nmea crate has a bug where it expects a trailing comma after the
    satellite count, but GSV sentences with 0 satellites end immediately
    at the checksum (e.g., $GPGSV,1,1,00*79).
    Work around by detecting these sentences and logging them at info level
    instead of trying to parse them. The GNTXT warnings are expected since
    text messages aren't enabled for navigation parsing.
2026-01-08 firmware: handle TXT sentences from GPS module
    TXT sentences (like GNTXT with antenna status) are status messages
    that the nmea crate doesn't fully parse. Log them at debug level
    instead of warning about parse failures.
2026-01-08 firmware: revert GPS NMEA parsing to original simple approach
    Reverted overcomplicated workarounds for GSV/TXT parsing. The original
    simple buffering approach works correctly - warnings are expected for
    unsupported sentence types but parsing still works for navigation data.
2026-01-08 firmware: suppress warnings for known NMEA parse failures
    GSV sentences with 0 satellites fail to parse due to nmea crate bug
    (missing trailing comma). TXT sentences are status messages we don't
    need. Suppress warnings for these known cases while keeping warnings
    for unexpected parse failures.
2026-01-08 firmware: remove TXT sentence filtering - warn on all parse errors
2026-01-08 feat: add multi-GNSS support and satellite info display
    Firmware:
    - Enable GPS + Galileo + BeiDou constellations via CFG-GNSS command
    - Add GnssType enum and SatelliteInfo struct for satellite details
    - Parse satellite data from NMEA GSV sentences (PRN, elevation, azimuth, SNR)
    - Add BLE characteristics for satellite info (2 chunks of 12 satellites each)
    - Broadcast satellite data via watch channels
2026-01-09 firmware: fix CFG-GNSS to include all 7 GNSS systems
    The MAX-M8Q module requires all 7 GNSS systems to be configured in the
    CFG-GNSS command. The previous 5-block configuration was being rejected
    (NAK), causing the module to use factory defaults (GPS + GLONASS only).
    Now correctly configures:
    - GPS: Enabled (8-16 channels)
    - SBAS: Disabled
2026-01-09 firmware: add gyroscope bias calibration to fix AHRS yaw drift
    The AHRS yaw was drifting continuously when the device was stationary
    due to uncorrected gyroscope bias. This commit adds:
    - GyroCalibration struct that computes average gyro bias during a
    4-second warmup period while the device is stationary
    - Bias correction is applied to all subsequent gyroscope readings
    - Removed magnetometer hard iron calibration (requires device rotation
